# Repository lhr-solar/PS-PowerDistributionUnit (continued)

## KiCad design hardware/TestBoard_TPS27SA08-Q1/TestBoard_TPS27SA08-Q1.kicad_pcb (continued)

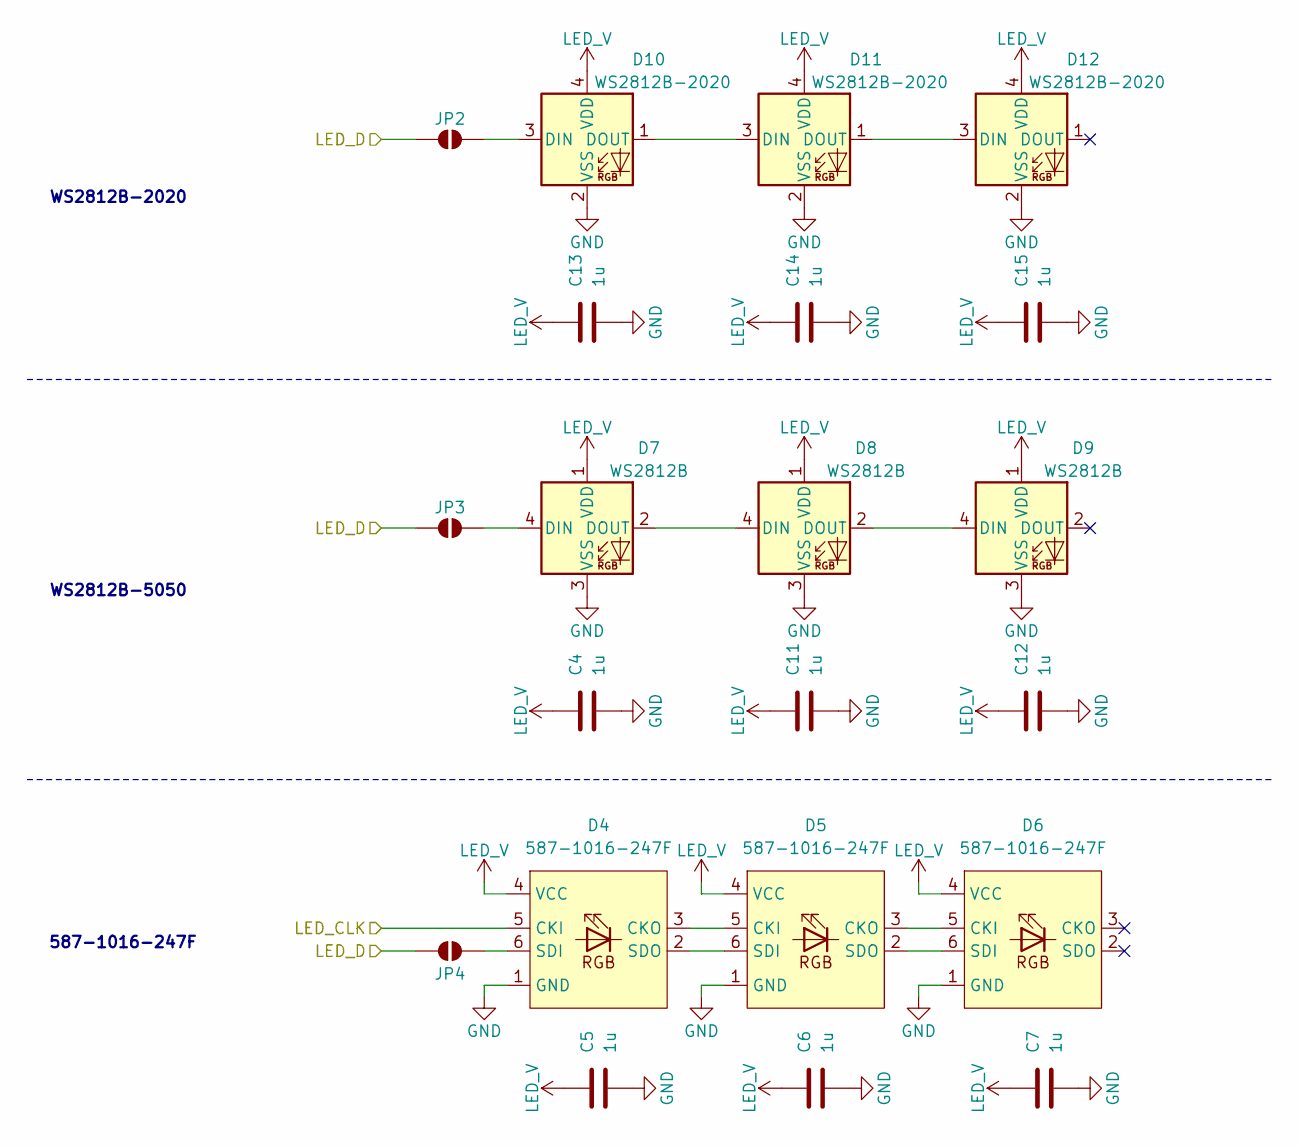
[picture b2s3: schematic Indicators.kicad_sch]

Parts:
C4, C5, C6, C7, C11, C12, C13, C14, C15: 1u; C_0603_1608Metric
D4, D5, D6: 587-1016-247F
D7, D8, D9: WS2812B; LED_WS2812B_PLCC4_5.0x5.0mm_P3.2mm
D10, D11, D12: WS2812B-2020; LED_WS2812B-2020_PLCC4_2.0x2.0mm
JP2, JP3, JP4: SolderJumper_2_Open; SolderJumper-2_P1.3mm_Open_RoundedPad1.0x1.5mm

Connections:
/LED_CK: D4.5 (CKI); also elsewhere on the board
/LED_D: JP2.1 (A), JP3.1 (A), JP4.1 (A); also elsewhere on the board
GND: C4.2, C5.2, C6.2, C7.2, C11.2, C12.2, C13.2, C14.2, C15.2, D4.1 (GND), D5.1 (GND), D6.1 (GND), D7.3 (VSS), D8.3 (VSS), D9.3 (VSS), D10.2 (VSS), D11.2 (VSS), D12.2 (VSS); also elsewhere on the board
LED_V: C4.1, C5.1, C6.1, C7.1, C11.1, C12.1, C13.1, C14.1, C15.1, D4.4 (VCC), D5.4 (VCC), D6.4 (VCC), D7.1 (VDD), D8.1 (VDD), D9.1 (VDD), D10.4 (VDD), D11.4 (VDD), D12.4 (VDD); also elsewhere on the board
unnamed: D4.3 (CKO), D5.5 (CKI)
unnamed: D4.6 (SDI), JP4.2 (B)
unnamed: D4.2 (SDO), D5.6 (SDI)
unnamed: D5.3 (CKO), D6.5 (CKI)
unnamed: D5.2 (SDO), D6.6 (SDI)
unnamed: D7.4 (DIN), JP3.2 (B)
unnamed: D7.2 (DOUT), D8.4 (DIN)
unnamed: D8.2 (DOUT), D9.4 (DIN)
unnamed: D10.3 (DIN), JP2.2 (B)
unnamed: D10.1 (DOUT), D11.3 (DIN)
unnamed: D11.1 (DOUT), D12.3 (DIN)

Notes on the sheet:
WS2812B-2020
WS2812B-5050
587-1016-247F

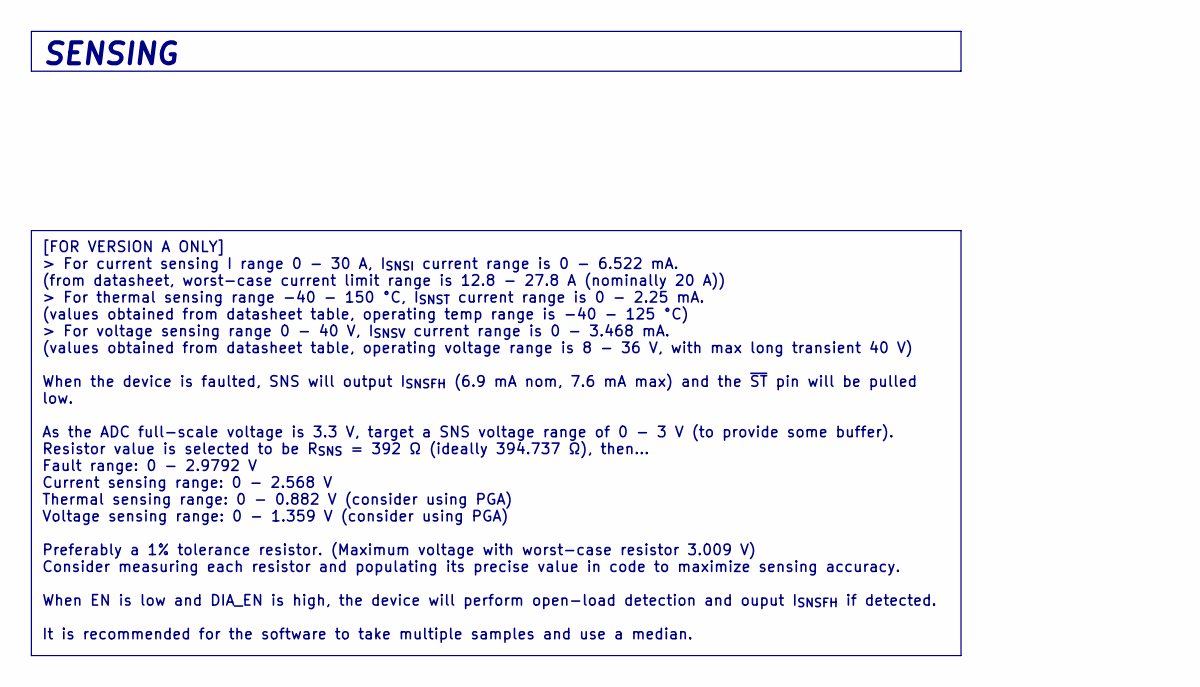
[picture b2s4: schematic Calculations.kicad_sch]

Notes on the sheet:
SENSING
[FOR VERSION A ONLY] > For current sensing I range 0 - 30 A, I_{SNSI} current range is 0 - 6.522 mA. (from datasheet, worst-case current limit range is 12.8 - 27.8 A (nominally 20 A)) > For thermal sensing range -40 - 150 °C, I_{SNST} current range is 0 - 2.25 mA. (values obtained from datasheet ta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

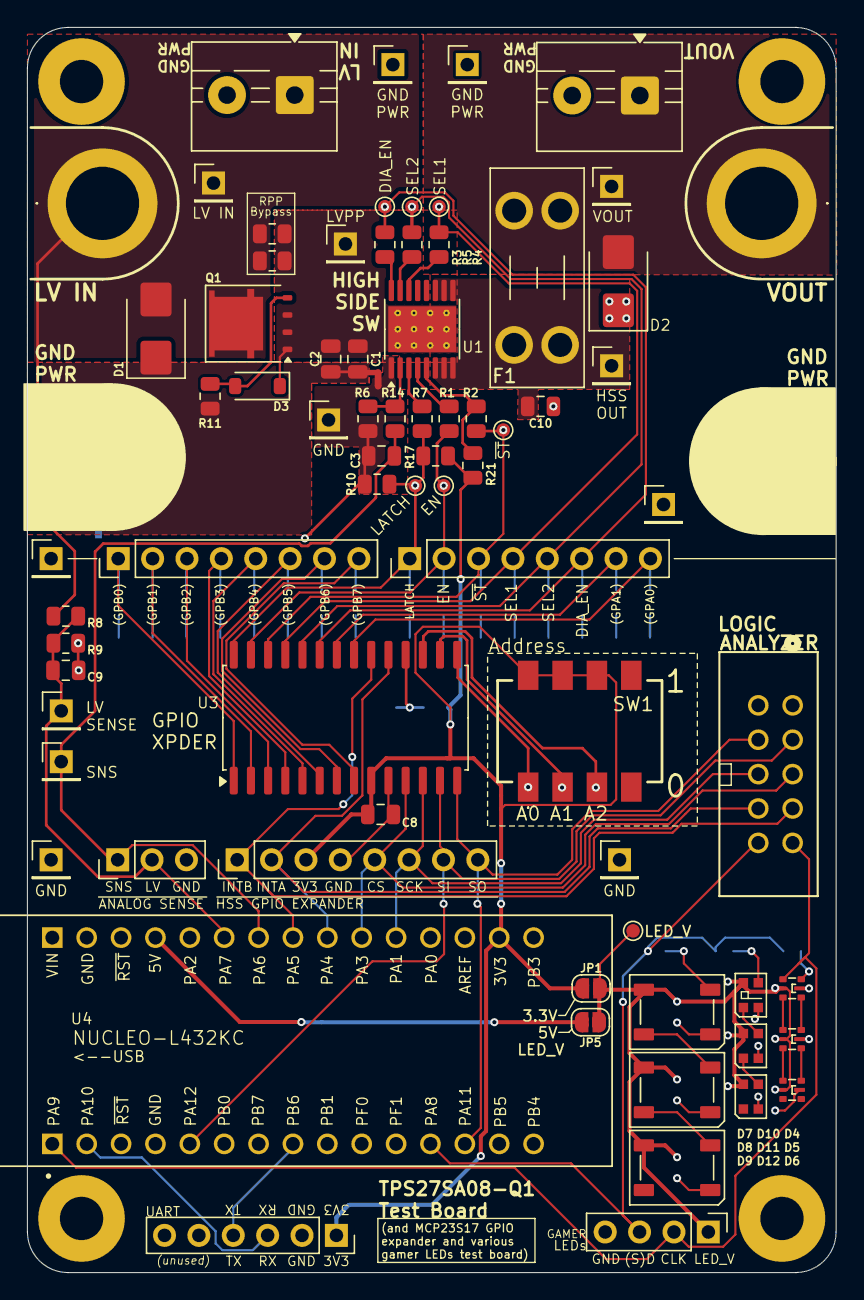
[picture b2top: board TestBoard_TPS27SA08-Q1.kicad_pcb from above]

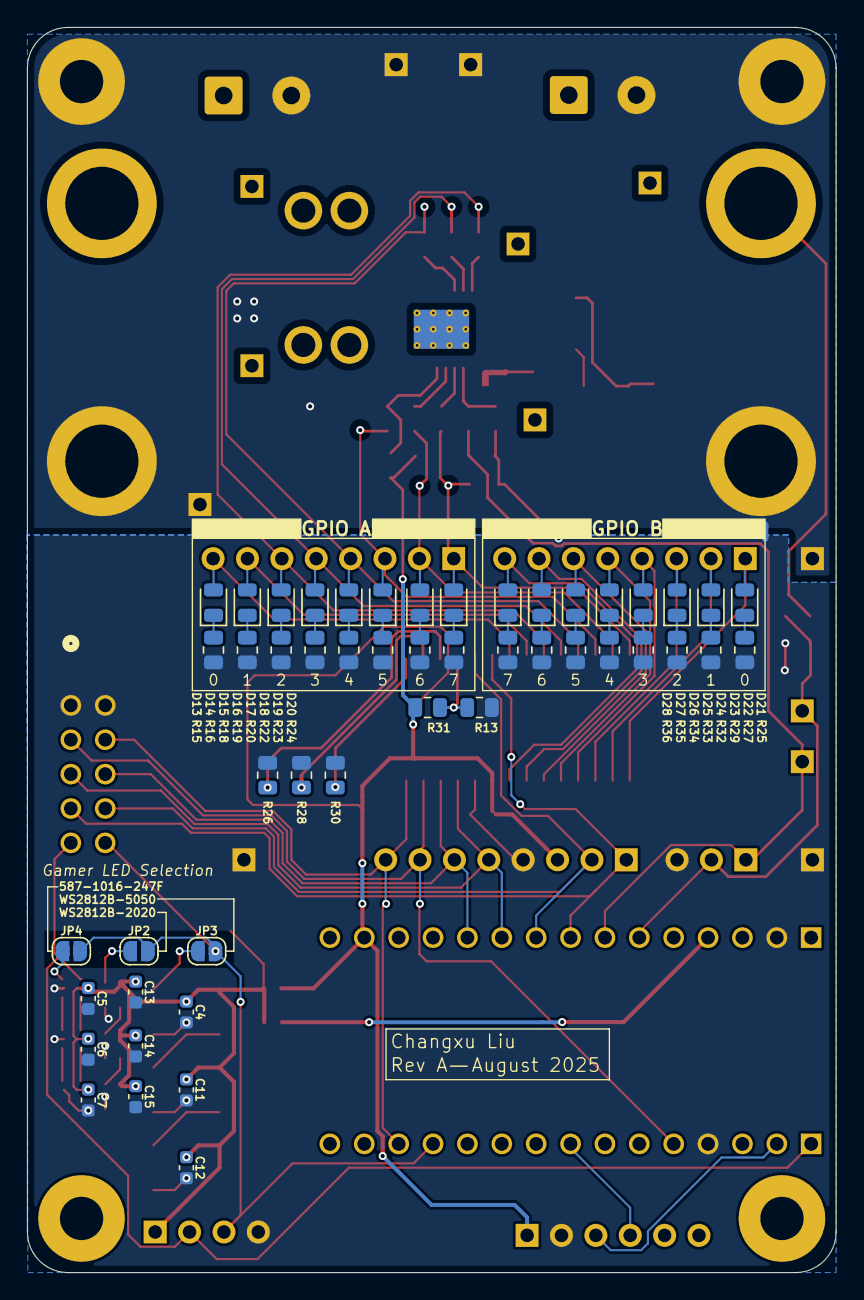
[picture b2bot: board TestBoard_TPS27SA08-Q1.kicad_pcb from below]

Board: 2 copper layers, 59.8 x 92.0 mm, 130 parts (50 on the bottom side), 76 nets.

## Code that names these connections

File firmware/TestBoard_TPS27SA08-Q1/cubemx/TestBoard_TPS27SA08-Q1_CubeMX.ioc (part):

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Mcu.Name=STM32L432K(B-C)Ux
Mcu.Package=UFQFPN32
Mcu.UserName=STM32L432KCUx
PA0.GPIOParameters=GPIO_Label
PA0.GPIO_Label=MCO [High speed clock in]
PA0.Mode=HSE-External-Clock-Source-for-LittleOrca
PA0.Signal=RCC_CK_IN
PA1.Mode=Full_Duplex_Master
PA1.Signal=SPI1_SCK
PA10.Mode=Asynchronous
PA10.Signal=USART1_RX
PA11.Mode=Full_Duplex_Master
PA11.Signal=SPI1_MISO
PA12.Mode=Full_Duplex_Master
PA12.Signal=SPI1_MOSI
PA13\ (JTMS-SWDIO).GPIOParameters=GPIO_Label
PA13\ (JTMS-SWDIO).GPIO_Label=SWDIO
PA13\ (JTMS-SWDIO).Mode=Serial_Wire
PA13\ (JTMS-SWDIO).Signal=SYS_JTMS-SWDIO
PA14\ (JTCK-SWCLK).GPIOParameters=GPIO_Label
PA14\ (JTCK-SWCLK).GPIO_Label=SWCLK
PA14\ (JTCK-SWCLK).Mode=Serial_Wire
PA14\ (JTCK-SWCLK).Signal=SYS_JTCK-SWCLK
PA15\ (JTDI).GPIOParameters=GPIO_Label
PA15\ (JTDI).GPIO_Label=VCP_RX
PA15\ (JTDI).Mode=Asynchronous
PA15\ (JTDI).Signal=USART2_RX
PA2.GPIOParameters=GPIO_Label
PA2.GPIO_Label=VCP_TX
PA2.Mode=Asynchronous
PA2.Signal=USART2_TX
PA3.Signal=GPIO_Output
PA4.Signal=GPIO_Output
PA5.Signal=GPIO_Output
PA6.Signal=ADCx_IN11
PA7.Signal=ADCx_IN12
PA8.Signal=S_TIM1_CH1
PA9.Signal=S_TIM1_CH2
PB3\ (JTDO-TRACESWO).GPIOParameters=GPIO_Label
PB3\ (JTDO-TRACESWO).GPIO_Label=LD3 [Green]
PB3\ (JTDO-TRACESWO).Signal=GPIO_Output
PB6.Mode=Asynchronous
PB6.Signal=USART1_TX
PC14-OSC32_IN\ (PC14).Mode=LSE-External-Oscillator
PC14-OSC32_IN\ (PC14).Signal=RCC_OSC32_IN
PC15-OSC32_OUT\ (PC15).Mode=LSE-External-Oscillator
PC15-OSC32_OUT\ (PC15).Signal=RCC_OSC32_OUT
RCC.HSE_VALUE=8000000
RCC.SYSCLKFreq_VALUE=32000000
RCC.SYSCLKSource=RCC_SYSCLKSOURCE_PLLCLK
board=NUCLEO-L432KC
boardIOC=true

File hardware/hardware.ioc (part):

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Mcu.Name=STM32G473C(B-C-E)Tx
Mcu.Package=LQFP48
Mcu.UserName=STM32G473CETx
PA0.Signal=GPIO_Output
PA15.Signal=GPIO_Output
PA3.Signal=GPIO_Output
PA4.Mode=NSS_Signal_Hard_Input
PA4.Signal=SPI1_NSS
PA5.Mode=Full_Duplex_Master
PA5.Signal=SPI1_SCK
PA6.Mode=Full_Duplex_Master
PA6.Signal=SPI1_MISO
PA7.Mode=Full_Duplex_Master
PA7.Signal=SPI1_MOSI
PA8.Signal=GPIO_Output
PA9.Signal=GPIO_Output
PB0.Signal=GPIO_Output
PB1.Signal=GPIO_Output
PB10.Signal=GPIO_Output
PB11.Signal=GPIO_Output
PB12.Mode=FDCAN_Activate
PB12.Signal=FDCAN2_RX
PB13.Mode=FDCAN_Activate
PB13.Signal=FDCAN2_TX
PB3.Signal=GPIO_Output
PB4.Signal=GPIO_Output
PB6.Signal=GPIO_Output
PB7.Signal=GPIO_Output
PC13.Signal=GPIO_Output
PC14-OSC32_IN.Signal=GPIO_Output
RCC.HSE_VALUE=8000000
RCC.SYSCLKFreq_VALUE=16000000
board=custom

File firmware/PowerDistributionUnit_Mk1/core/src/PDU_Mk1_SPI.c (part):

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
        __HAL_RCC_GPIOA_CLK_ENABLE();
        /**SPI1 GPIO Configuration
        PA5     ------> SPI1_SCK
        PA6     ------> SPI1_MISO
        PA7     ------> SPI1_MOSI
        */
        GPIO_InitStruct.Pin = GPIO_PIN_5|GPIO_PIN_6|GPIO_PIN_7;
        GPIO_InitStruct.Mode = GPIO_MODE_AF_PP;
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
        __HAL_RCC_GPIOB_CLK_ENABLE();
        /**SPI2 GPIO Configuration
        PB13     ------> SPI2_SCK
        PB14     ------> SPI2_MISO
        PB15     ------> SPI2_MOSI
        */
        GPIO_InitStruct.Pin = GPIO_PIN_13|GPIO_PIN_14|GPIO_PIN_15;
        GPIO_InitStruct.Mode = GPIO_MODE_AF_PP;
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
        __HAL_RCC_GPIOB_CLK_ENABLE();
        /**SPI3 GPIO Configuration
        PB3     ------> SPI3_SCK
        PB4     ------> SPI3_MISO
        PB5     ------> SPI3_MOSI
        */
        GPIO_InitStruct.Pin = GPIO_PIN_3|GPIO_PIN_4|GPIO_PIN_5;
        GPIO_InitStruct.Mode = GPIO_MODE_AF_PP;
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	__HAL_RCC_SPI1_CLK_DISABLE();

	/**SPI1 GPIO Configuration
	PA5     ------> SPI1_SCK
	PA6     ------> SPI1_MISO
	PA7     ------> SPI1_MOSI
	*/
	HAL_GPIO_DeInit(GPIOA, GPIO_PIN_5|GPIO_PIN_6|GPIO_PIN_7);
	}
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	__HAL_RCC_SPI2_CLK_DISABLE();

	/**SPI2 GPIO Configuration
	PB13     ------> SPI2_SCK
	PB14     ------> SPI2_MISO
	PB15     ------> SPI2_MOSI
	*/
	HAL_GPIO_DeInit(GPIOB, GPIO_PIN_13|GPIO_PIN_14|GPIO_PIN_15);
	}
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	__HAL_RCC_SPI3_CLK_DISABLE();

	/**SPI3 GPIO Configuration
	PB3     ------> SPI3_SCK
	PB4     ------> SPI3_MISO
	PB5     ------> SPI3_MOSI
	*/
	HAL_GPIO_DeInit(GPIOB, GPIO_PIN_3|GPIO_PIN_4|GPIO_PIN_5);
	}
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
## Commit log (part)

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2025-10-20 LED to LSOM and logic analyzer connector routing
2025-10-20 gnd test points placement and added some
2025-10-20 change gnd return to 6 pin nanofit
2025-10-20 make a couple gnd test points gndpwr, fix silkscreen separation, move test points inwards to keep silkscreen on PCB
2025-10-20 added external current sensor
2025-10-20 break bottom tracks between two sides of efuses
2025-10-20 break output tracks'
2025-10-20 shift sides of HSSs outwards
2025-10-20 one current sensor routing
2025-10-20 add physical fuse, routing for one output
2025-10-20 one quarter HSS routed
2025-10-20 one half HSS routed
2025-10-20 other side HSS add current sensor
2025-10-20 routing left side st and sns
2025-10-20 oops forgot sns5
2025-10-20 output traces
2025-10-21 st and adc traces on computery side, prep for pin/adc reassignment
2025-10-21 reassigned pins for connecting HSS to sensing
2025-10-21 routed sensing traces
2025-10-21 all connections routed
2025-10-21 reposition top side connectors (CAN, logic analyzer) and make board slightly taller
2025-10-23 adjust spacing on logic analyzer connectors
2025-10-23 readjust gnd plane to new size
2025-10-23 adjust two adc traces to reduce via clearance cutouts on gnd planes
2025-10-25 status LEDs position adjustment, silkscreen, address DRC errors in that area
2025-10-25 rearrange 3.3V, 3.3VA, and GNDA test points, add labels for test points around LSOM, address DRC errors in area (and some LED ones that came back for some reason)
2025-10-25 cleaned up HSS config and regional area
2025-10-25 clean up and address DRC errors in input area
2025-10-25 remove PCB silkscreen clearance requirements
2025-10-25 cleaning up things on/around LSOM
2025-10-25 top and bottom side silkscreen under LSOM
2025-10-25 add labels for some stuff
2025-10-25 make logic analyzer connector fancy
2025-10-25 HSSs area silkscreen DRCs
2025-10-25 address trace unconnected ends in DRC
2025-10-25 clear real clearance errors
2025-10-25 change input protection MOSFET
2025-10-25 fix wonky traces
2025-10-25 move fuse label over
2025-10-25 excluded unnecessary clearance drc errors
2025-10-26 added HSS output labels
2025-10-26 add bypass to lv sense buffer
2025-10-26 add P/Ns to external current sensor symbol
2025-10-26 add labels for HSS pulls
2025-10-26 add title and logos
2025-10-26 move gnd return connector upwards to free up more lv plane
2025-10-26 add random stitching vias
2025-10-26 fillet corners in edge cuts
2025-10-26 add Darsh responsibility statement
2025-10-26 ensure DRC is clear
2025-10-28 fix current sensor part number (used 5V version instead of 3.3V version)
2025-11-09 export gerbers
2026-01-16 BBPDU Mk1 (#4)
    * add KiCad project
    * initial schematic
    * fix gamer LED footprint thing, thanks Gemini
    * change new symbol libraries to relative paths, thanks Gemini
    * schematic updates (found switch, LED resistor values, LV sense ADC pin filter, removed unnecessary parallel resistors, switched to new SR), addressed review comments (input fuse, 3.3V LED, SPI nami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
    * fix pages order, fix duplicate C25
2026-01-16 rename software folder to firmware
2026-01-17 set up embedded sharepoint
2026-01-31 MCP23S17 GPIO expander driver
2026-01-31 update makefile to give build failure message, remove madefile when running make clean
2026-01-31 add blank line to nix_thing.sh
2026-02-28 change ADC - reading voltage to resistor divider with option to reference to GND or 1.65V
2026-02-28 update adc reference to use internal reference (open) with jumper option
2026-02-28 change ADC AVDD and AGND connections to regular 3.3V and GND
2026-02-28 update KiCad-Sharepoint
2026-02-28 reroute LSOM SPI connections, repin logic analyzer connections
2026-02-28 change LSOM footprint to centered LSOM footprint, make centered LSOM footprint plated to address hidden pins on LSOM symbol
2026-02-28 update LeaderSOM symbol and SPI pinout (bottom) - need to swap SPI2 and SPI3 names, remove local library copy of LeaderSOM symbol
2026-02-28 layout/routing for input protection
2026-02-28 fix centered LSOM footprint 3D model, update footprint
2026-02-28 address DRC
2026-02-28 route a couple of missed connections (LV in connection to input prot IC, LV sense connection)
2026-02-28 change jumper to DNP resistor for ADC reference, routed
2026-02-28 reroute updated AVDD and AGND on ADCs
2026-02-28 add SRCLK_ENed connection to logic analyzer connector
2026-02-28 silkscreen fixes and stuff
2026-02-28 fix silkscreen labelling issues
2026-02-28 update schematic documentation, clean up, update titleblocks
2026-03-01 add LCSC P/N to libs
2026-03-01 update all symbols with LCSC P/N
2026-03-01 update PCB with LCSC P/Ns
2026-03-01 correct SR part number to SOIC package
2026-03-01 correct fuse table
2026-03-02 change lv sense rdiv values to avoid extended components, update all pull-ups/-downs using 2.8k
2026-03-02 rotate nanofits for inwards clip
2026-03-02 NC the mounting holes (because Lakshay Gupta)
2026-03-02 assembly setup, change latch pull resistor DNP to latch off instead of auto retry by default
2026-03-02 silkscreen stuff
2026-03-02 change DNP for HSS diagnostics to default to current
2026-03-02 change DNP to disable HSS diagnostics by default (primarily use external current sensor)
2026-03-03 BBPDU Mk1 RevB (#6)
    * update adc reference to use internal reference (open) with jumper option
    * change ADC - reading voltage to resistor divider with option to reference to GND or 1.65V
    * change ADC AVDD and AGND connections to regular 3.3V and GND
    * make input protection use b2b FETs
    * update KiCad-Sharepoint
    * update LeaderSOM symbol and SPI pinout (bottom) - need to swap SPI2 and SPI3 names, remove local library copy of LeaderSOM symbol
2026-03-03 add new PDTestBreakout project
2026-03-03 schematic, add symbol/footprint for screw terminal and banana connector
2026-03-06 fix TEST capitalization in makefile, change formatting
2026-03-06 add MCP23S17 datasheet
2026-03-07 add register descriptions
2026-03-07 add enum comments
2026-03-07 address addressing double left-shift, comments
2026-03-07 move defines out of c file to header file
2026-03-07 update function documentation comments, add comments for static functions in c file
2026-03-07 function comment update
2026-03-07 change functions to return status
2026-03-07 make more functions return status
2026-03-08 update documentation returning status, other things
2026-03-08 move uint8_to_binary_str to utilities file
2026-03-08 add pin defines to file
2026-03-13 add descriptions to tests
2026-03-13 add blank lines
2026-03-31 add todo
2026-04-02 add basic RTOS support, update a few tests alongside
2026-04-02 fix hard coded fsr value
2026-04-02 fix reading zero registers in Init function (still in progress)
2026-04-04 add _t to type names for enums and structs
2026-04-04 update constant names, update comments, clean up
2026-04-04 update MCP23S17 init function for less arguments, change configuration to use lshift, comments and stuff, cleanup
2026-04-05 updated MCP23S17 test for RTOS - untested as don't have TestBoard_TPS27SA08-Q1 with me, just getting to compiling to test build action
2026-04-05 add github build action
2026-04-05 add github build action (attempt 2)
2026-04-05 add github build action (attempt 4)
2026-04-05 add github build action (attempt 5)
2026-04-05 add github build action (attempt 6)
2026-04-05 remove commies.c
2026-04-05 add _t to enum and struct type names
2026-04-05 add units to SPI delay names
2026-04-05 fix tests
2026-04-05 change Pins, SPI, and UART files structure
2026-04-06 add device and data null check
2026-04-06 move CS stuff to static inline function
2026-04-06 lakshay being picky picky picky
2026-04-06 fix spi cs and mutex not returning to original state if spi transmission semaphore times out
2026-04-06 fix discarding status return if not 🙂 (as now there's more statuses)
2026-04-06 fix spi cs and mutex not returning to original state if HAL spi function isn't happy
2026-04-06 put SPI message length into variable
2026-04-06 add checks for spi mutex and sempahore null
2026-04-06 move SPI interrupt functions ot SPI file
2026-04-06 move SPI mutex and done semaphore setup to function in SPI file
2026-04-07 add flash-uart to makefile
2026-04-11 move init stuff to separate files, try consolidating ADC testing into one test
2026-04-11 must've forgotten to include this in update to define name from before
2026-04-12 ADC driver init function, calibration register functions
2026-04-12 move private functions to c file
2026-04-12 Add embedded sharepoint, MCP23S17 driver and basic tests (#5)
    * rename software folder to firmware
    * set up embedded sharepoint
    * fix makefile showing flash successful even when not (fix in Embedded-Sharepoint)
    * MCP23S17 GPIO expander driver
    * update makefile to give build failure message, remove madefile when running make clean
    * add blank line to nix_thing.sh
2026-04-25 move mutex stuff out of frame function, update frame function to have different functions for tx/rx/txrx, add checks for null data pointer, etc.
2026-04-25 fix reset command delay in wrong spot
2026-04-25 add other enums for SPI mutex/semaphore timeouts
2026-04-25 change numbers in one test to be defines, make reference voltage value a define, remove debug return in init that resulted in no configuration written
2026-04-25 update adc init function to update all channels, address task stack overflow issues in test
2026-04-25 remove commented out for loop replaced with memset
2026-04-25 oops didn't actually incrase stack size before
2026-04-25 update ADS131M08Q1 tests (and LSOM blinky printy)
2026-04-25 add documentation comments, fix declaration name of a transmit function
2026-04-26 fix SPI potentially being trapped if CS or mutex not released in case of failure
2026-04-26 change CS delay value to a define
2026-04-26 remove magic number
2026-05-08 add current sensing with ADC initialization moved to
2026-05-10 update Convert test and initialization for both ADCs on BBPDU
2026-05-10 add check for SPI and SPI RTOS stuff set up properly before attempting talking with ADC
2026-05-10 fix trying to printf before UART is configured
2026-05-10 update embedded sharepoint
2026-05-10 add all the ADS131M08-Q1 driver stuff from before...
2026-05-10 attempt add github action
2026-05-10 try github action again
2026-05-10 attempt github action again
2026-05-10 fix copy paste errors in SPI
2026-05-10 fix convoluted conversion code
2026-05-10 ADS131M08-Q1 driver (#10)
    (see PR #7)
    * add all the ADS131M08-Q1 driver stuff from before...
    * attempt add github action
    * try github action again
    * attempt github action again
    * fix copy paste errors in SPI
2026-05-10 current sensing code
2026-05-10 fix copy paste errors in current sensing header
2026-05-11 remove underscore between current sensing
2026-05-11 HSS control
2026-05-17 add fs
2026-05-17 remove disable interrupts from test error handler
2026-05-17 add description and example part number, add datasheet
2026-05-17 add function descriptions, fix typo in driver description
2026-05-17 remove debug printf statements
2026-05-17 add warning on keeping everything within one task for HSSControl to description
2026-05-20 remove filtering faulted channels from output en
2026-06-21 add conditional to avoid trying to use inaccessible ADC on rev A (pinout issue)
2026-06-22 add SPI reconfiguration function before communicating with ADC
2026-06-22 add SPI reconfiguration function before communicating with SR
2026-06-22 add functions for getting EN and fault state of a channel (for CAN stuff)
2026-06-22 update indentation
2026-06-24 add comment on ReconfigSPI usage
2026-06-24 HSS control (#12)
    * HSS control
    * remove disable interrupts from test error handler
    * add description and example part number, add datasheet
    * update delay
    * add function descriptions, fix typo in driver description
    * remove debug printf statements
2026-06-25 Current sensing (#11)
    * current sensing code
    * fix copy paste errors in current sensing header
    * make initial offset calculation average of multiple samples
    * remove underscore between current sensing
    * add fs
    * add conditional to avoid trying to use inaccessible ADC on rev A (pinout issue)
2026-06-25 CAN and tasks stuff
2026-06-25 remove old tests because causing Github check to fail
2026-06-26 add void argument for RTOS tasks
2026-06-26 remove redundant while(1)
2026-06-26 fix HSS Control task description
2026-06-26 remove unused print status task for now
